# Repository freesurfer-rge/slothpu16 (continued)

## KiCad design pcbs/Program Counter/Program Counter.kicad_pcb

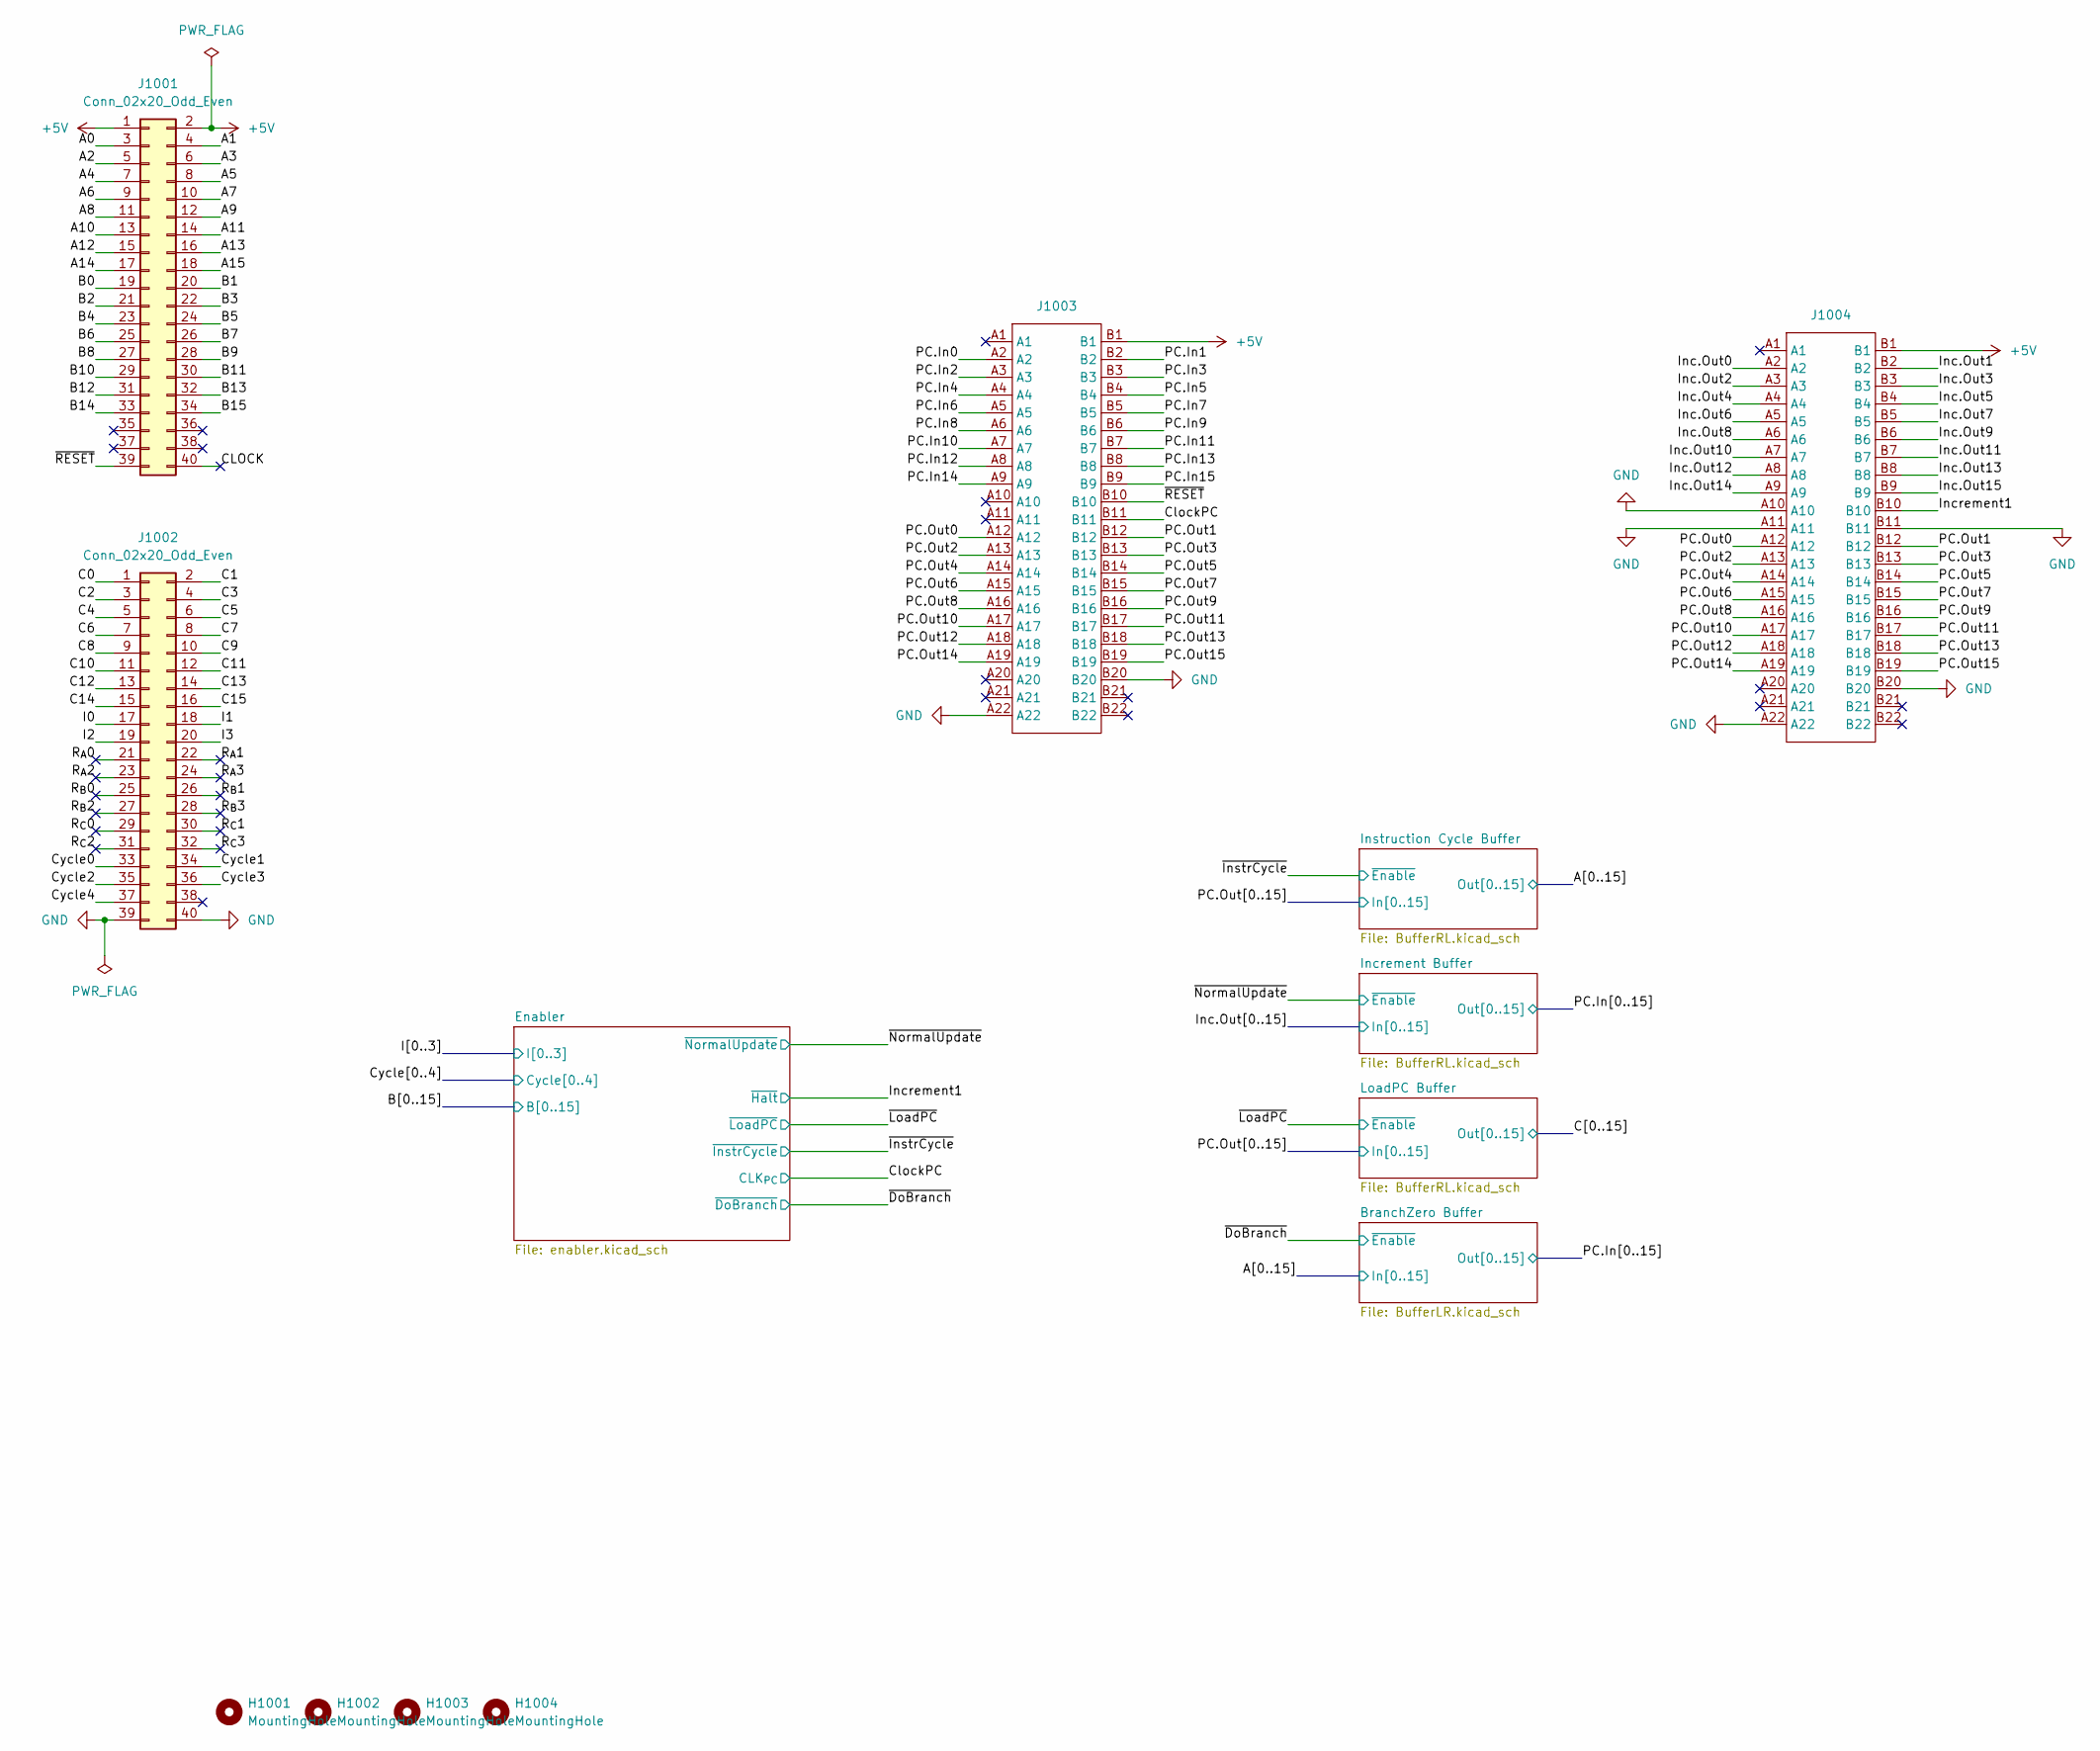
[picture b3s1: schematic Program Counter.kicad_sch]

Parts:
H1001, H1002, H1003, H1004: MountingHole; MountingHole_2.7mm_M2.5_ISO7380
J1001, J1002: Conn_02x20_Odd_Even; PinHeader_2x20_P2.54mm_Vertical
J1003, J1004: TE-5530843-4-Mount

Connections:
+5V: J1001.1, J1001.2, J1003.B1, J1004.B1; also elsewhere on the board
/A0: J1001.3; also elsewhere on the board
/A1: J1001.4; also elsewhere on the board
/A2: J1001.5; also elsewhere on the board
/A3: J1001.6; also elsewhere on the board
/A4: J1001.7; also elsewhere on the board
/A5: J1001.8; also elsewhere on the board
/A6: J1001.9; also elsewhere on the board
/A7: J1001.10; also elsewhere on the board
/A8: J1001.11; also elsewhere on the board
/A9: J1001.12; also elsewhere on the board
/A10: J1001.13; also elsewhere on the board
/A11: J1001.14; also elsewhere on the board
/A12: J1001.15; also elsewhere on the board
/A13: J1001.16; also elsewhere on the board
/A14: J1001.17; also elsewhere on the board
/A15: J1001.18; also elsewhere on the board
/B0: J1001.19; also elsewhere on the board
/B1: J1001.20; also elsewhere on the board
/B2: J1001.21; also elsewhere on the board
/B3: J1001.22; also elsewhere on the board
/B4: J1001.23; also elsewhere on the board
/B5: J1001.24; also elsewhere on the board
/B6: J1001.25; also elsewhere on the board
/B7: J1001.26; also elsewhere on the board
/B8: J1001.27; also elsewhere on the board
/B9: J1001.28; also elsewhere on the board
/B10: J1001.29; also elsewhere on the board
/B11: J1001.30; also elsewhere on the board
/B12: J1001.31; also elsewhere on the board
/B13: J1001.32; also elsewhere on the board
/B14: J1001.33; also elsewhere on the board
/B15: J1001.34; also elsewhere on the board
/C0: J1002.1; also elsewhere on the board
/C1: J1002.2; also elsewhere on the board
/C2: J1002.3; also elsewhere on the board
/C3: J1002.4; also elsewhere on the board
/C4: J1002.5; also elsewhere on the board
/C5: J1002.6; also elsewhere on the board
/C6: J1002.7; also elsewhere on the board
/C7: J1002.8; also elsewhere on the board
/C8: J1002.9; also elsewhere on the board
/C9: J1002.10; also elsewhere on the board
/C10: J1002.11; also elsewhere on the board
/C11: J1002.12; also elsewhere on the board
/C12: J1002.13; also elsewhere on the board
/C13: J1002.14; also elsewhere on the board
/C14: J1002.15; also elsewhere on the board
/C15: J1002.16; also elsewhere on the board
/CLOCK: J1001.40
/ClockPC: J1003.B11; also elsewhere on the board
/Cycle0: J1002.33; also elsewhere on the board
/Cycle1: J1002.34; also elsewhere on the board
/Cycle2: J1002.35; also elsewhere on the board
/Cycle3: J1002.36; also elsewhere on the board
/Cycle4: J1002.37; also elsewhere on the board
/I0: J1002.17; also elsewhere on the board
/I1: J1002.18; also elsewhere on the board
/I2: J1002.19; also elsewhere on the board
/I3: J1002.20; also elsewhere on the board
/Inc.Out0: J1004.A2; also elsewhere on the board
/Inc.Out1: J1004.B2; also elsewhere on the board
/Inc.Out2: J1004.A3; also elsewhere on the board
/Inc.Out3: J1004.B3; also elsewhere on the board
/Inc.Out4: J1004.A4; also elsewhere on the board
/Inc.Out5: J1004.B4; also elsewhere on the board
/Inc.Out6: J1004.A5; also elsewhere on the board
/Inc.Out7: J1004.B5; also elsewhere on the board
/Inc.Out8: J1004.A6; also elsewhere on the board
/Inc.Out9: J1004.B6; also elsewhere on the board
/Inc.Out10: J1004.A7; also elsewhere on the board
/Inc.Out11: J1004.B7; also elsewhere on the board
/Inc.Out12: J1004.A8; also elsewhere on the board
/Inc.Out13: J1004.B8; also elsewhere on the board
/Inc.Out14: J1004.A9; also elsewhere on the board
/Inc.Out15: J1004.B9; also elsewhere on the board
/Increment1: J1004.B10; also elsewhere on the board
/PC.In0: J1003.A2; also elsewhere on the board
/PC.In1: J1003.B2; also elsewhere on the board
/PC.In2: J1003.A3; also elsewhere on the board
/PC.In3: J1003.B3; also elsewhere on the board
/PC.In4: J1003.A4; also elsewhere on the board
/PC.In5: J1003.B4; also elsewhere on the board
/PC.In6: J1003.A5; also elsewhere on the board
/PC.In7: J1003.B5; also elsewhere on the board
/PC.In8: J1003.A6; also elsewhere on the board
/PC.In9: J1003.B6; also elsewhere on the board
/PC.In10: J1003.A7; also elsewhere on the board
/PC.In11: J1003.B7; also elsewhere on the board
/PC.In12: J1003.A8; also elsewhere on the board
/PC.In13: J1003.B8; also elsewhere on the board
/PC.In14: J1003.A9; also elsewhere on the board
/PC.In15: J1003.B9; also elsewhere on the board
/PC.Out0: J1003.A12, J1004.A12; also elsewhere on the board
/PC.Out1: J1003.B12, J1004.B12; also elsewhere on the board
/PC.Out2: J1003.A13, J1004.A13; also elsewhere on the board
/PC.Out3: J1003.B13, J1004.B13; also elsewhere on the board
/PC.Out4: J1003.A14, J1004.A14; also elsewhere on the board
/PC.Out5: J1003.B14, J1004.B14; also elsewhere on the board
/PC.Out6: J1003.A15, J1004.A15; also elsewhere on the board
/PC.Out7: J1003.B15, J1004.B15; also elsewhere on the board
/PC.Out8: J1003.A16, J1004.A16; also elsewhere on the board
/PC.Out9: J1003.B16, J1004.B16; also elsewhere on the board
/PC.Out10: J1003.A17, J1004.A17; also elsewhere on the board
/PC.Out11: J1003.B17, J1004.B17; also elsewhere on the board
/PC.Out12: J1003.A18, J1004.A18; also elsewhere on the board
/PC.Out13: J1003.B18, J1004.B18; also elsewhere on the board
/PC.Out14: J1003.A19, J1004.A19; also elsewhere on the board
/PC.Out15: J1003.B19, J1004.B19; also elsewhere on the board
/R_{A}0: J1002.21
/R_{A}1: J1002.22
/R_{A}2: J1002.23
/R_{A}3: J1002.24
/R_{B}0: J1002.25
/R_{B}1: J1002.26
/R_{B}2: J1002.27
/R_{B}3: J1002.28
/R_{C}0: J1002.29
/R_{C}1: J1002.30
/R_{C}2: J1002.31
/R_{C}3: J1002.32
/~RESET: J1001.39, J1003.B10
GND: J1002.39, J1002.40, J1003.A22, J1003.B20, J1004.A10, J1004.A11, J1004.A22, J1004.B11, J1004.B20; also elsewhere on the board

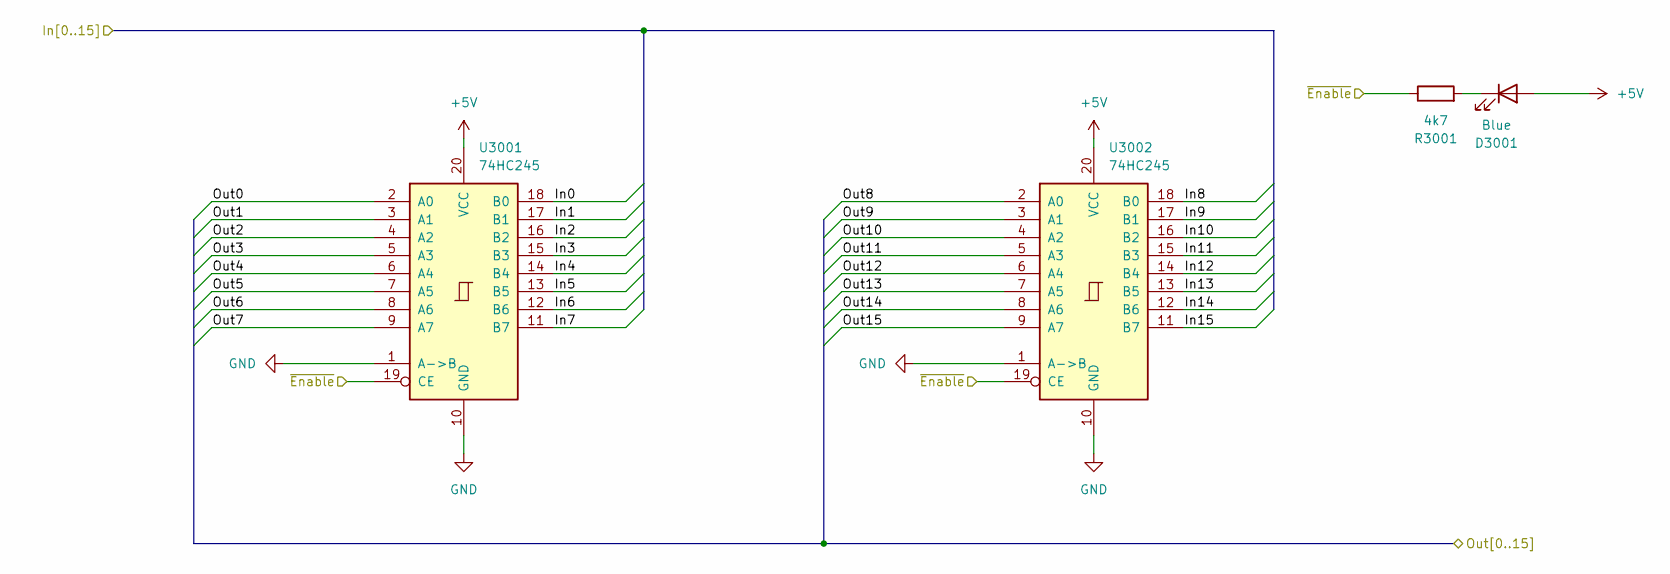
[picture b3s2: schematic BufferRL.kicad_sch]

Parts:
D3001: Blue; LED_0603_1608Metric; LCSC C72041
R3001: 4k7; R_0603_1608Metric; LCSC C23162
U3001, U3002: 74HC245; SOIC-20W_7.5x12.8mm_P1.27mm; LCSC C5625

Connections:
+5V: D3001.2 (A), U3001.20 (VCC), U3002.20 (VCC); also elsewhere on the board
/Inc.Out0: U3001.18 (B0); also elsewhere on the board
/Inc.Out1: U3001.17 (B1); also elsewhere on the board
/Inc.Out2: U3001.16 (B2); also elsewhere on the board
/Inc.Out3: U3001.15 (B3); also elsewhere on the board
/Inc.Out4: U3001.14 (B4); also elsewhere on the board
/Inc.Out5: U3001.13 (B5); also elsewhere on the board
/Inc.Out6: U3001.12 (B6); also elsewhere on the board
/Inc.Out7: U3001.11 (B7); also elsewhere on the board
/Inc.Out8: U3002.18 (B0); also elsewhere on the board
/Inc.Out9: U3002.17 (B1); also elsewhere on the board
/Inc.Out10: U3002.16 (B2); also elsewhere on the board
/Inc.Out11: U3002.15 (B3); also elsewhere on the board
/Inc.Out12: U3002.14 (B4); also elsewhere on the board
/Inc.Out13: U3002.13 (B5); also elsewhere on the board
/Inc.Out14: U3002.12 (B6); also elsewhere on the board
/Inc.Out15: U3002.11 (B7); also elsewhere on the board
/PC.In0: U3001.2 (A0); also elsewhere on the board
/PC.In1: U3001.3 (A1); also elsewhere on the board
/PC.In2: U3001.4 (A2); also elsewhere on the board
/PC.In3: U3001.5 (A3); also elsewhere on the board
/PC.In4: U3001.6 (A4); also elsewhere on the board
/PC.In5: U3001.7 (A5); also elsewhere on the board
/PC.In6: U3001.8 (A6); also elsewhere on the board
/PC.In7: U3001.9 (A7); also elsewhere on the board
/PC.In8: U3002.2 (A0); also elsewhere on the board
/PC.In9: U3002.3 (A1); also elsewhere on the board
/PC.In10: U3002.4 (A2); also elsewhere on the board
/PC.In11: U3002.5 (A3); also elsewhere on the board
/PC.In12: U3002.6 (A4); also elsewhere on the board
/PC.In13: U3002.7 (A5); also elsewhere on the board
/PC.In14: U3002.8 (A6); also elsewhere on the board
/PC.In15: U3002.9 (A7); also elsewhere on the board
/~NormalUpdate: R3001.1, U3001.19 (CE), U3002.19 (CE); also elsewhere on the board
GND: U3001.1 (A->B), U3001.10 (GND), U3002.1 (A->B), U3002.10 (GND); also elsewhere on the board
unnamed: D3001.1 (K), R3001.2

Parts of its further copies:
D2001, D4001: Blue; LED_0603_1608Metric; LCSC C72041
R2001, R4001: 4k7; R_0603_1608Metric; LCSC C23162
U2001, U2002, U4001, U4002: 74HC245; SOIC-20W_7.5x12.8mm_P1.27mm; LCSC C5625

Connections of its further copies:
+5V: D2001.2 (A), D4001.2 (A), U2001.20 (VCC), U2002.20 (VCC), U4001.20 (VCC), U4002.20 (VCC); also elsewhere on the board
/A0: U2001.2 (A0); also elsewhere on the board
/A1: U2001.3 (A1); also elsewhere on the board
/A2: U2001.4 (A2); also elsewhere on the board
/A3: U2001.5 (A3); also elsewhere on the board
/A4: U2001.6 (A4); also elsewhere on the board
/A5: U2001.7 (A5); also elsewhere on the board
/A6: U2001.8 (A6); also elsewhere on the board
/A7: U2001.9 (A7); also elsewhere on the board
/A8: U2002.2 (A0); also elsewhere on the board
/A9: U2002.3 (A1); also elsewhere on the board
/A10: U2002.4 (A2); also elsewhere on the board
/A11: U2002.5 (A3); also elsewhere on the board
/A12: U2002.6 (A4); also elsewhere on the board
/A13: U2002.7 (A5); also elsewhere on the board
/A14: U2002.8 (A6); also elsewhere on the board
/A15: U2002.9 (A7); also elsewhere on the board
/C0: U4001.2 (A0); also elsewhere on the board
/C1: U4001.3 (A1); also elsewhere on the board
/C2: U4001.4 (A2); also elsewhere on the board
/C3: U4001.5 (A3); also elsewhere on the board
/C4: U4001.6 (A4); also elsewhere on the board
/C5: U4001.7 (A5); also elsewhere on the board
/C6: U4001.8 (A6); also elsewhere on the board
/C7: U4001.9 (A7); also elsewhere on the board
/C8: U4002.2 (A0); also elsewhere on the board
/C9: U4002.3 (A1); also elsewhere on the board
/C10: U4002.4 (A2); also elsewhere on the board
/C11: U4002.5 (A3); also elsewhere on the board
/C12: U4002.6 (A4); also elsewhere on the board
/C13: U4002.7 (A5); also elsewhere on the board
/C14: U4002.8 (A6); also elsewhere on the board
/C15: U4002.9 (A7); also elsewhere on the board
/PC.Out0: U2001.18 (B0), U4001.18 (B0); also elsewhere on the board
/PC.Out1: U2001.17 (B1), U4001.17 (B1); also elsewhere on the board
/PC.Out2: U2001.16 (B2), U4001.16 (B2); also elsewhere on the board
/PC.Out3: U2001.15 (B3), U4001.15 (B3); also elsewhere on the board
/PC.Out4: U2001.14 (B4), U4001.14 (B4); also elsewhere on the board
/PC.Out5: U2001.13 (B5), U4001.13 (B5); also elsewhere on the board
/PC.Out6: U2001.12 (B6), U4001.12 (B6); also elsewhere on the board
/PC.Out7: U2001.11 (B7), U4001.11 (B7); also elsewhere on the board
/PC.Out8: U2002.18 (B0), U4002.18 (B0); also elsewhere on the board
/PC.Out9: U2002.17 (B1), U4002.17 (B1); also elsewhere on the board
/PC.Out10: U2002.16 (B2), U4002.16 (B2); also elsewhere on the board
/PC.Out11: U2002.15 (B3), U4002.15 (B3); also elsewhere on the board
/PC.Out12: U2002.14 (B4), U4002.14 (B4); also elsewhere on the board
/PC.Out13: U2002.13 (B5), U4002.13 (B5); also elsewhere on the board
/PC.Out14: U2002.12 (B6), U4002.12 (B6); also elsewhere on the board
/PC.Out15: U2002.11 (B7), U4002.11 (B7); also elsewhere on the board
/~InstrCycle: R2001.1, U2001.19 (CE), U2002.19 (CE); also elsewhere on the board
/~LoadPC: R4001.1, U4001.19 (CE), U4002.19 (CE); also elsewhere on the board
GND: U2001.1 (A->B), U2001.10 (GND), U2002.1 (A->B), U2002.10 (GND), U4001.1 (A->B), U4001.10 (GND), U4002.1 (A->B), U4002.10 (GND); also elsewhere on the board
unnamed: D2001.1 (K), R2001.2
unnamed: D4001.1 (K), R4001.2

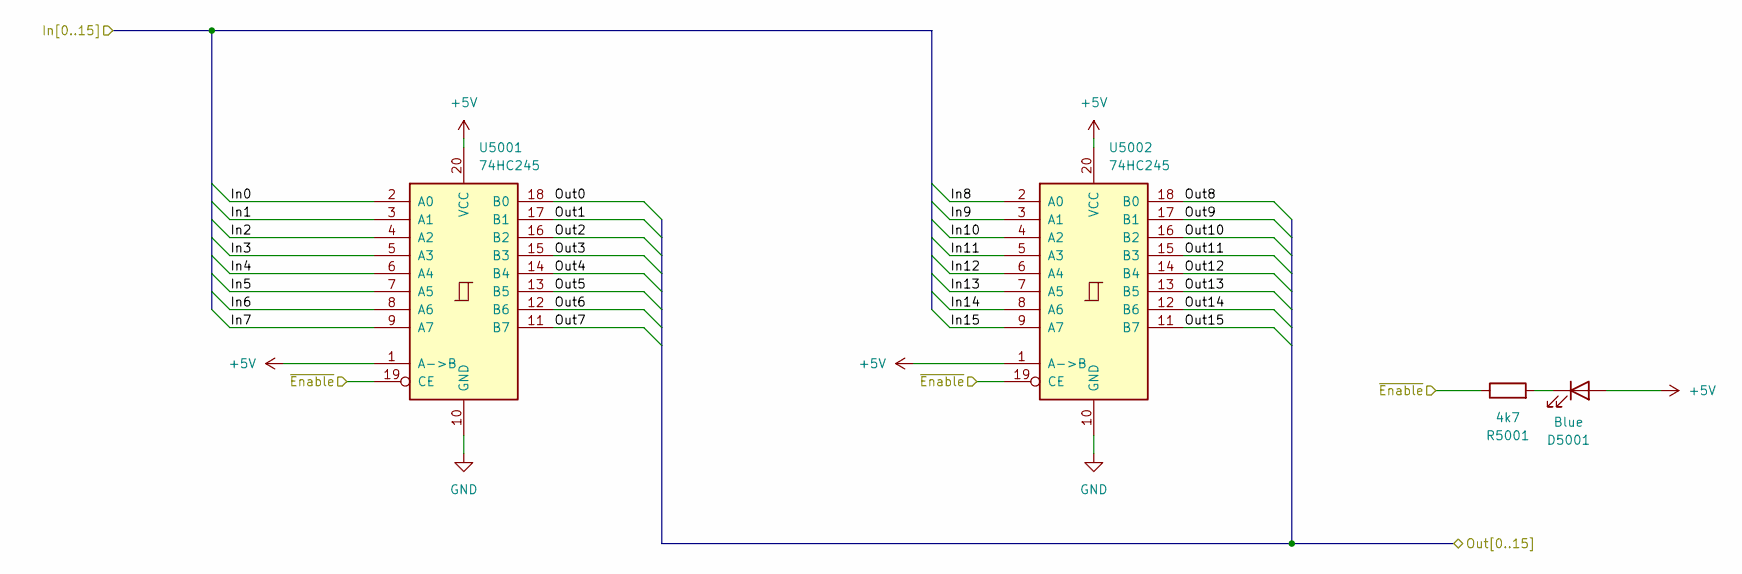
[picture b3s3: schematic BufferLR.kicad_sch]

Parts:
D5001: Blue; LED_0603_1608Metric; LCSC C72041
R5001: 4k7; R_0603_1608Metric; LCSC C23162
U5001, U5002: 74HC245; SOIC-20W_7.5x12.8mm_P1.27mm; LCSC C5625

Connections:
+5V: D5001.2 (A), U5001.1 (A->B), U5001.20 (VCC), U5002.1 (A->B), U5002.20 (VCC); also elsewhere on the board
/A0: U5001.2 (A0); also elsewhere on the board
/A1: U5001.3 (A1); also elsewhere on the board
/A2: U5001.4 (A2); also elsewhere on the board
/A3: U5001.5 (A3); also elsewhere on the board
/A4: U5001.6 (A4); also elsewhere on the board
/A5: U5001.7 (A5); also elsewhere on the board
/A6: U5001.8 (A6); also elsewhere on the board
/A7: U5001.9 (A7); also elsewhere on the board
/A8: U5002.2 (A0); also elsewhere on the board
/A9: U5002.3 (A1); also elsewhere on the board
/A10: U5002.4 (A2); also elsewhere on the board
/A11: U5002.5 (A3); also elsewhere on the board
/A12: U5002.6 (A4); also elsewhere on the board
/A13: U5002.7 (A5); also elsewhere on the board
/A14: U5002.8 (A6); also elsewhere on the board
/A15: U5002.9 (A7); also elsewhere on the board
/PC.In0: U5001.18 (B0); also elsewhere on the board
/PC.In1: U5001.17 (B1); also elsewhere on the board
/PC.In2: U5001.16 (B2); also elsewhere on the board
/PC.In3: U5001.15 (B3); also elsewhere on the board
/PC.In4: U5001.14 (B4); also elsewhere on the board
/PC.In5: U5001.13 (B5); also elsewhere on the board
/PC.In6: U5001.12 (B6); also elsewhere on the board
/PC.In7: U5001.11 (B7); also elsewhere on the board
/PC.In8: U5002.18 (B0); also elsewhere on the board
/PC.In9: U5002.17 (B1); also elsewhere on the board
/PC.In10: U5002.16 (B2); also elsewhere on the board
/PC.In11: U5002.15 (B3); also elsewhere on the board
/PC.In12: U5002.14 (B4); also elsewhere on the board
/PC.In13: U5002.13 (B5); also elsewhere on the board
/PC.In14: U5002.12 (B6); also elsewhere on the board
/PC.In15: U5002.11 (B7); also elsewhere on the board
/~DoBranch: R5001.1, U5001.19 (CE), U5002.19 (CE); also elsewhere on the board
GND: U5001.10 (GND), U5002.10 (GND); also elsewhere on the board
unnamed: D5001.1 (K), R5001.2

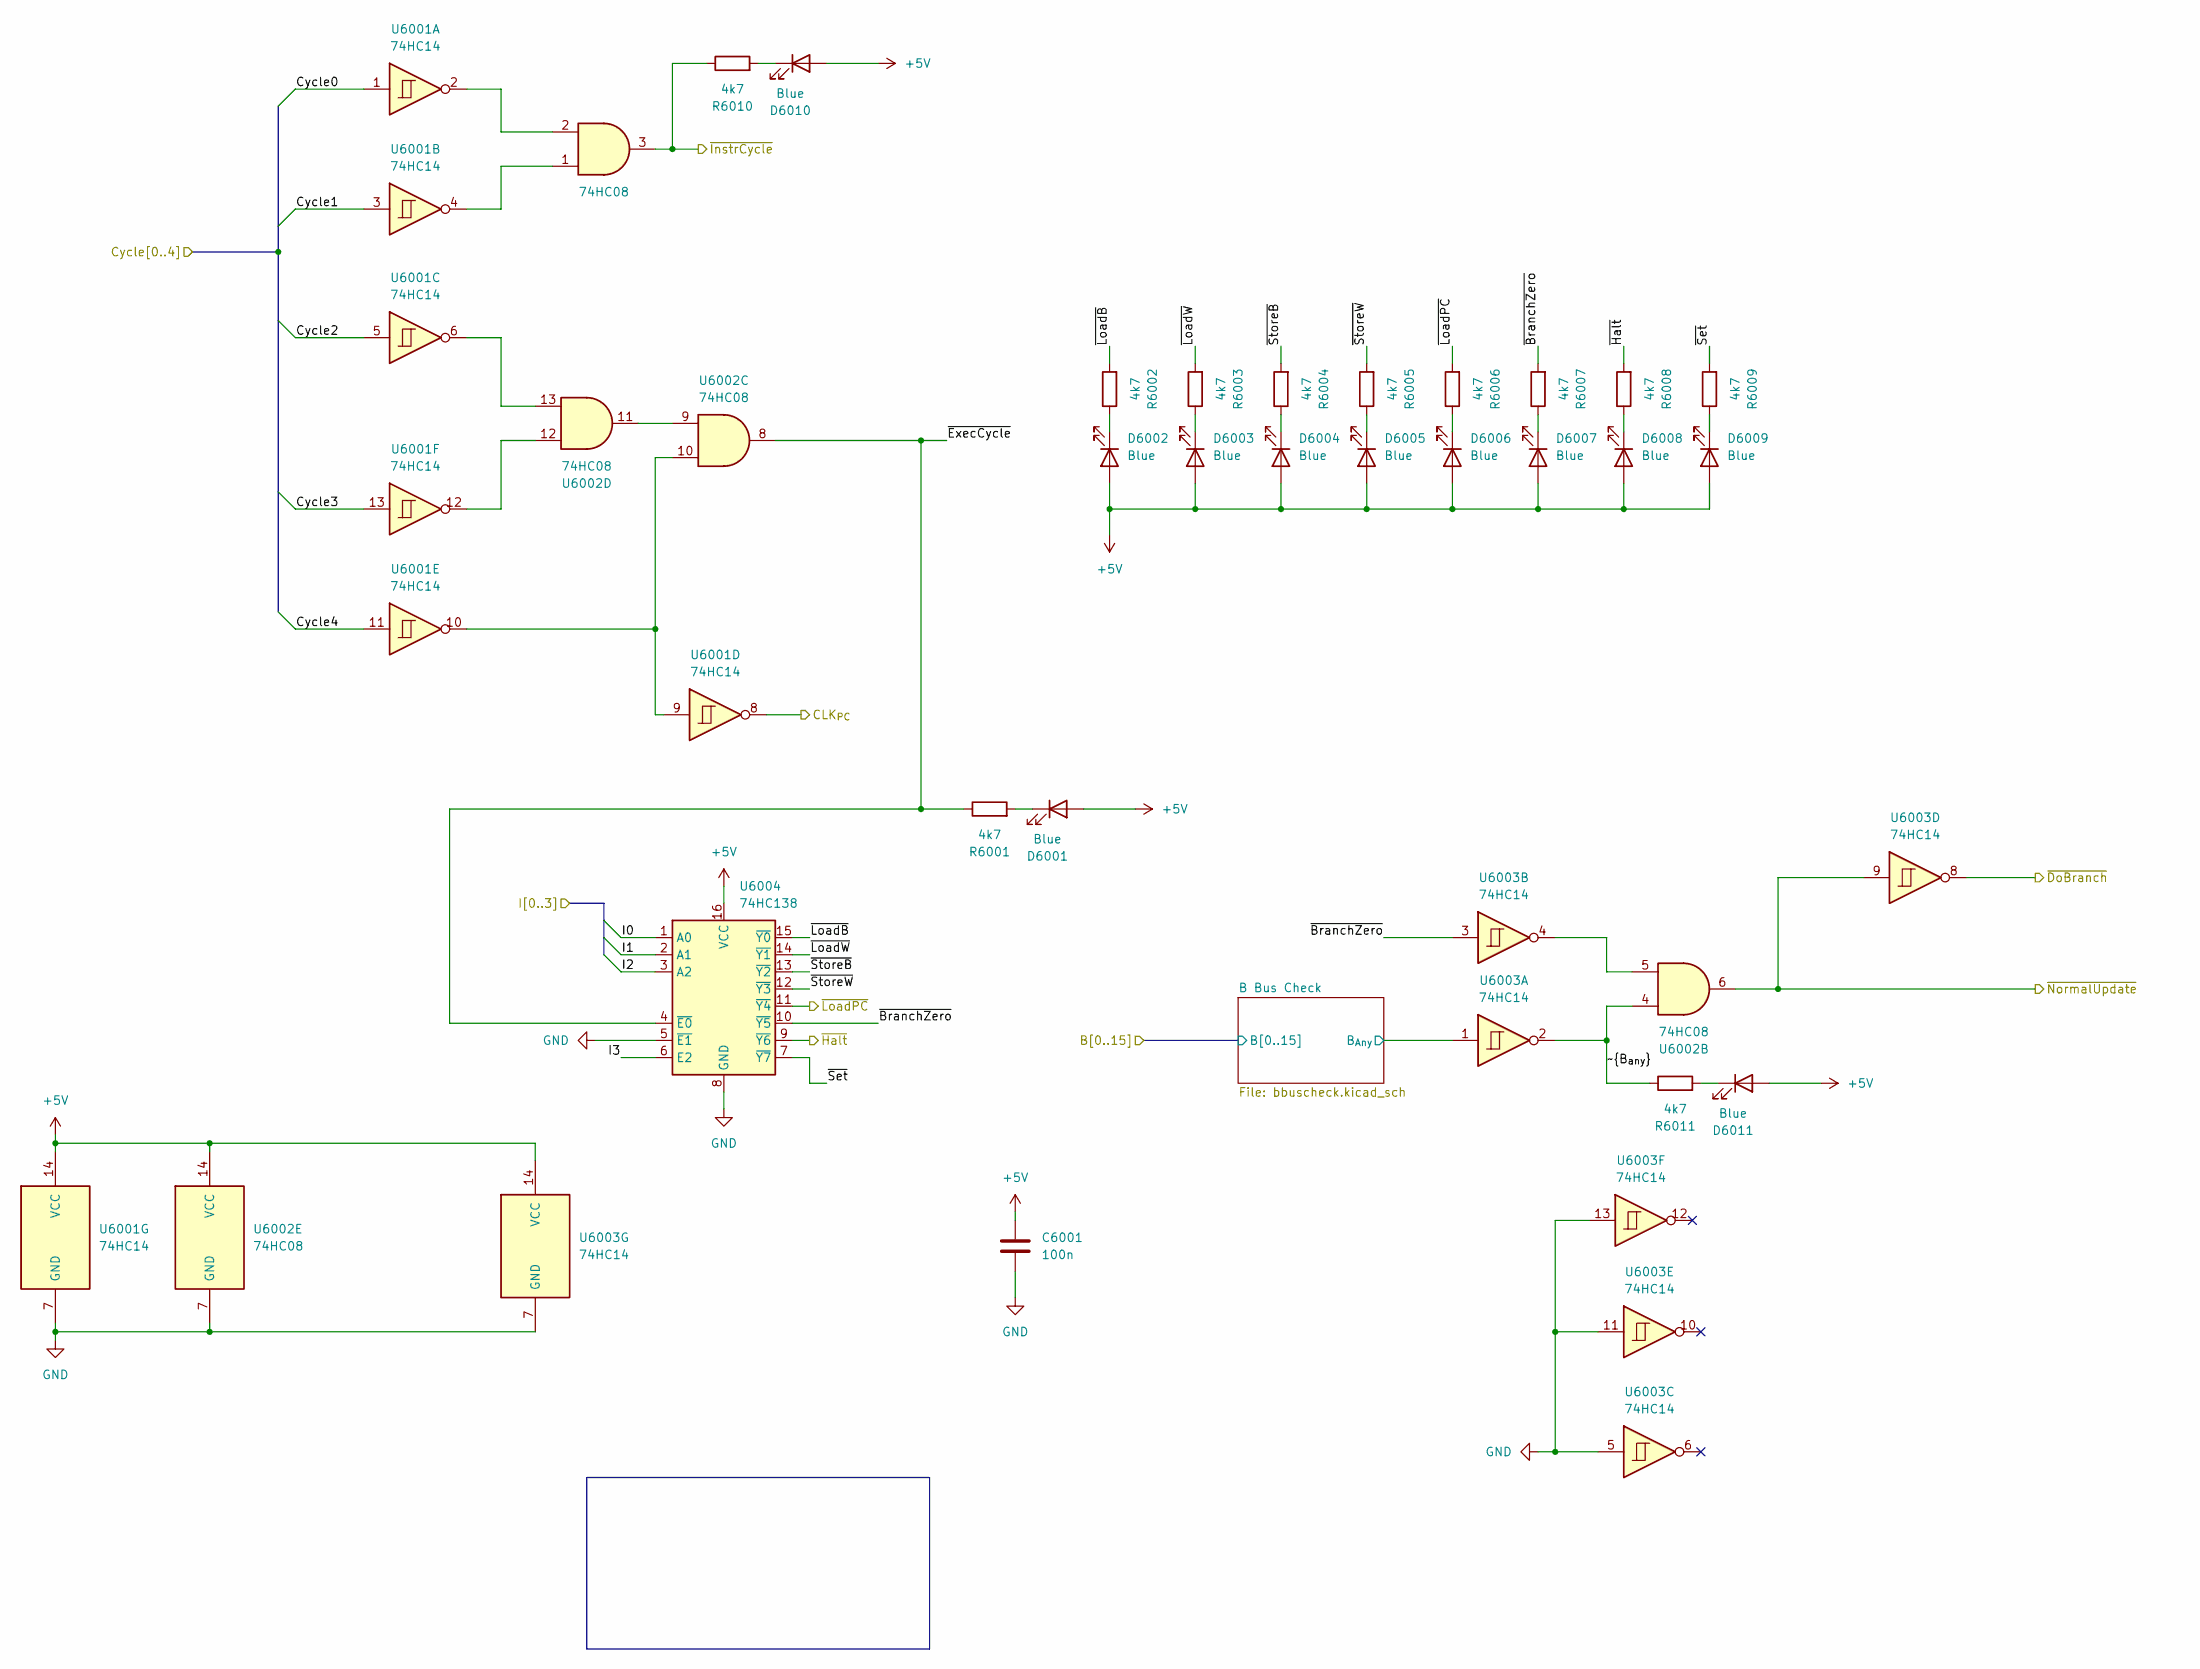
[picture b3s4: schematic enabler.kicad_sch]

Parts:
C6001: 100n; C_0603_1608Metric; LCSC C14663
D6001, D6002, D6003, D6004, D6005, D6006, D6007, D6008, D6009, D6010, D6011: Blue; LED_0603_1608Metric; LCSC C72041
R6001, R6002, R6003, R6004, R6005, R6006, R6007, R6008, R6009, R6010, R6011: 4k7; R_0603_1608Metric; LCSC C23162
U6001, U6003: 74HC14; SOIC-14_3.9x8.7mm_P1.27mm; LCSC C5605
U6002: 74HC08; SOIC-14_3.9x8.7mm_P1.27mm; LCSC C5593
U6004: 74HC138; DIP-16_W7.62mm_Socket

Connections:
+5V: C6001.1, D6001.2 (A), D6002.2 (A), D6003.2 (A), D6004.2 (A), D6005.2 (A), D6006.2 (A), D6007.2 (A), D6008.2 (A), D6009.2 (A), D6010.2 (A), D6011.2 (A), U6001.14 (VCC), U6002.14 (VCC), U6003.14 (VCC), U6004.16 (VCC); also elsewhere on the board
/ClockPC: U6001.8; also elsewhere on the board
/Cycle0: U6001.1; also elsewhere on the board
/Cycle1: U6001.3; also elsewhere on the board
/Cycle2: U6001.5; also elsewhere on the board
/Cycle3: U6001.13; also elsewhere on the board
/Cycle4: U6001.11; also elsewhere on the board
/Enabler/B Bus Check/B_{Any}: U6003.1; also elsewhere on the board
/Enabler/~B_{any}: R6011.1, U6002.4, U6003.2
/Enabler/~BranchZero: R6007.2, U6003.3, U6004.10 (~Y5)
/Enabler/~ExecCycle: R6001.1, U6002.8, U6004.4 (~E0)
/Enabler/~LoadB: R6002.2, U6004.15 (~Y0)
/Enabler/~LoadW: R6003.2, U6004.14 (~Y1)
/Enabler/~Set: R6009.2, U6004.7 (~Y7)
/Enabler/~StoreB: R6004.2, U6004.13 (~Y2)
/Enabler/~StoreW: R6005.2, U6004.12 (~Y3)
/I0: U6004.1 (A0); also elsewhere on the board
/I1: U6004.2 (A1); also elsewhere on the board
/I2: U6004.3 (A2); also elsewhere on the board
/I3: U6004.6 (E2); also elsewhere on the board
/Increment1: R6008.2, U6004.9 (~Y6); also elsewhere on the board
/~DoBranch: U6003.8; also elsewhere on the board
/~InstrCycle: R6010.1, U6002.3; also elsewhere on the board
/~LoadPC: R6006.2, U6004.11 (~Y4); also elsewhere on the board
/~NormalUpdate: U6002.6, U6003.9; also elsewhere on the board
GND: C6001.2, U6001.7 (GND), U6002.7 (GND), U6003.5, U6003.7 (GND), U6003.11, U6003.13, U6004.5 (~E1), U6004.8 (GND); also elsewhere on the board
unnamed: D6001.1 (K), R6001.2
unnamed: D6002.1 (K), R6002.1
unnamed: D6003.1 (K), R6003.1
unnamed: D6004.1 (K), R6004.1
unnamed: D6005.1 (K), R6005.1
unnamed: D6006.1 (K), R6006.1
unnamed: D6007.1 (K), R6007.1
unnamed: D6008.1 (K), R6008.1
unnamed: D6009.1 (K), R6009.1
unnamed: D6010.1 (K), R6010.2
unnamed: D6011.1 (K), R6011.2
unnamed: U6001.2, U6002.2
unnamed: U6001.4, U6002.1
unnamed: U6001.6, U6002.13
unnamed: U6001.9, U6001.10, U6002.10
unnamed: U6001.12, U6002.12
unnamed: U6002.5, U6003.4
unnamed: U6002.9, U6002.11

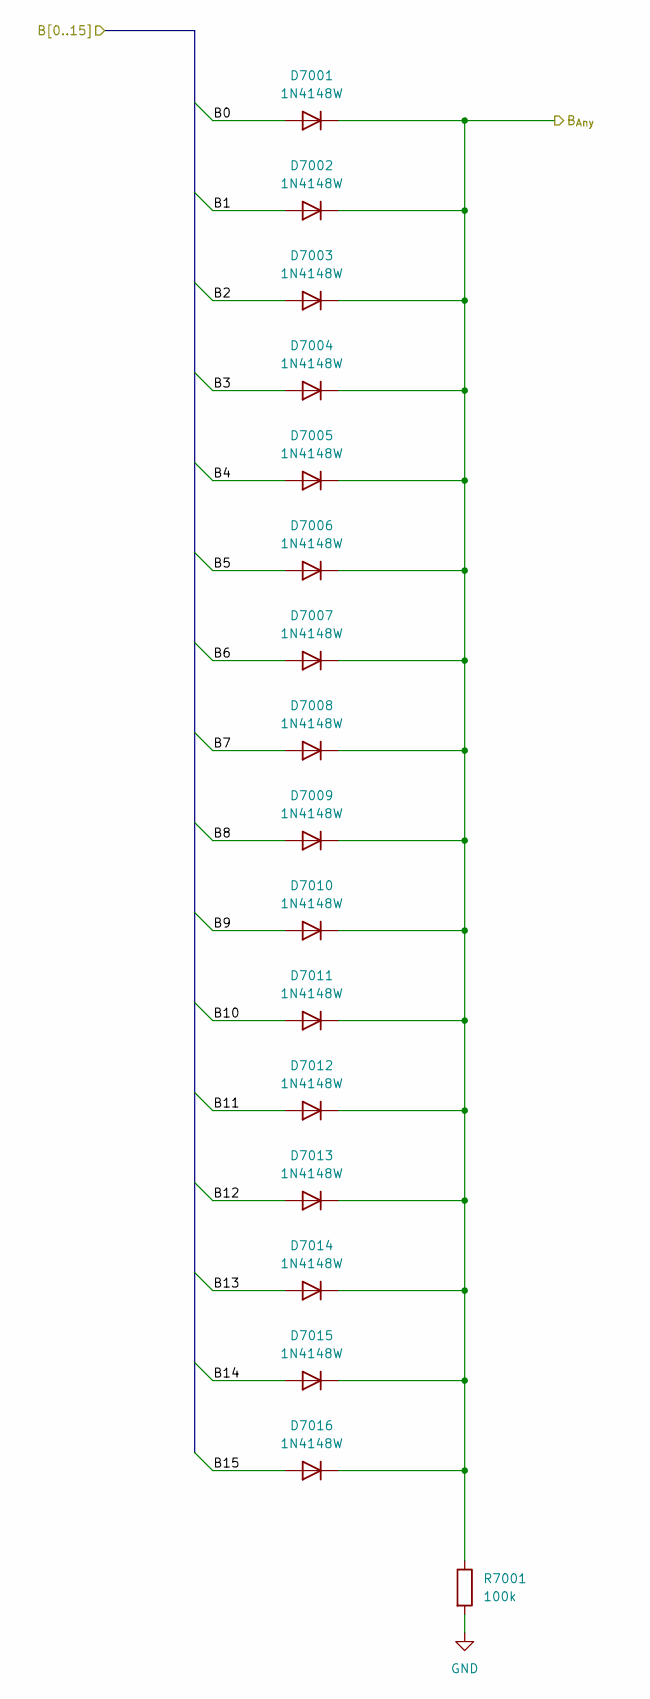
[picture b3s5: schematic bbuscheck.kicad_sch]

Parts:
D7001, D7002, D7003, D7004, D7005, D7006, D7007, D7008, D7009, D7010, D7011, D7012, D7013, D7014, D7015, D7016: 1N4148W; D_SOD-323; LCSC C2128
R7001: 100k; R_0603_1608Metric; LCSC C25803

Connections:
/B0: D7001.2 (A); also elsewhere on the board
/B1: D7002.2 (A); also elsewhere on the board
/B2: D7003.2 (A); also elsewhere on the board
/B3: D7004.2 (A); also elsewhere on the board
/B4: D7005.2 (A); also elsewhere on the board
/B5: D7006.2 (A); also elsewhere on the board
/B6: D7007.2 (A); also elsewhere on the board
/B7: D7008.2 (A); also elsewhere on the board
/B8: D7009.2 (A); also elsewhere on the board
/B9: D7010.2 (A); also elsewhere on the board
/B10: D7011.2 (A); also elsewhere on the board
/B11: D7012.2 (A); also elsewhere on the board
/B12: D7013.2 (A); also elsewhere on the board
/B13: D7014.2 (A); also elsewhere on the board
/B14: D7015.2 (A); also elsewhere on the board
/B15: D7016.2 (A); also elsewhere on the board
/Enabler/B Bus Check/B_{Any}: D7001.1 (K), D7002.1 (K), D7003.1 (K), D7004.1 (K), D7005.1 (K), D7006.1 (K), D7007.1 (K), D7008.1 (K), D7009.1 (K), D7010.1 (K), D7011.1 (K), D7012.1 (K), D7013.1 (K), D7014.1 (K), D7015.1 (K), D7016.1 (K), R7001.1; also elsewhere on the board
GND: R7001.2; also elsewhere on the board

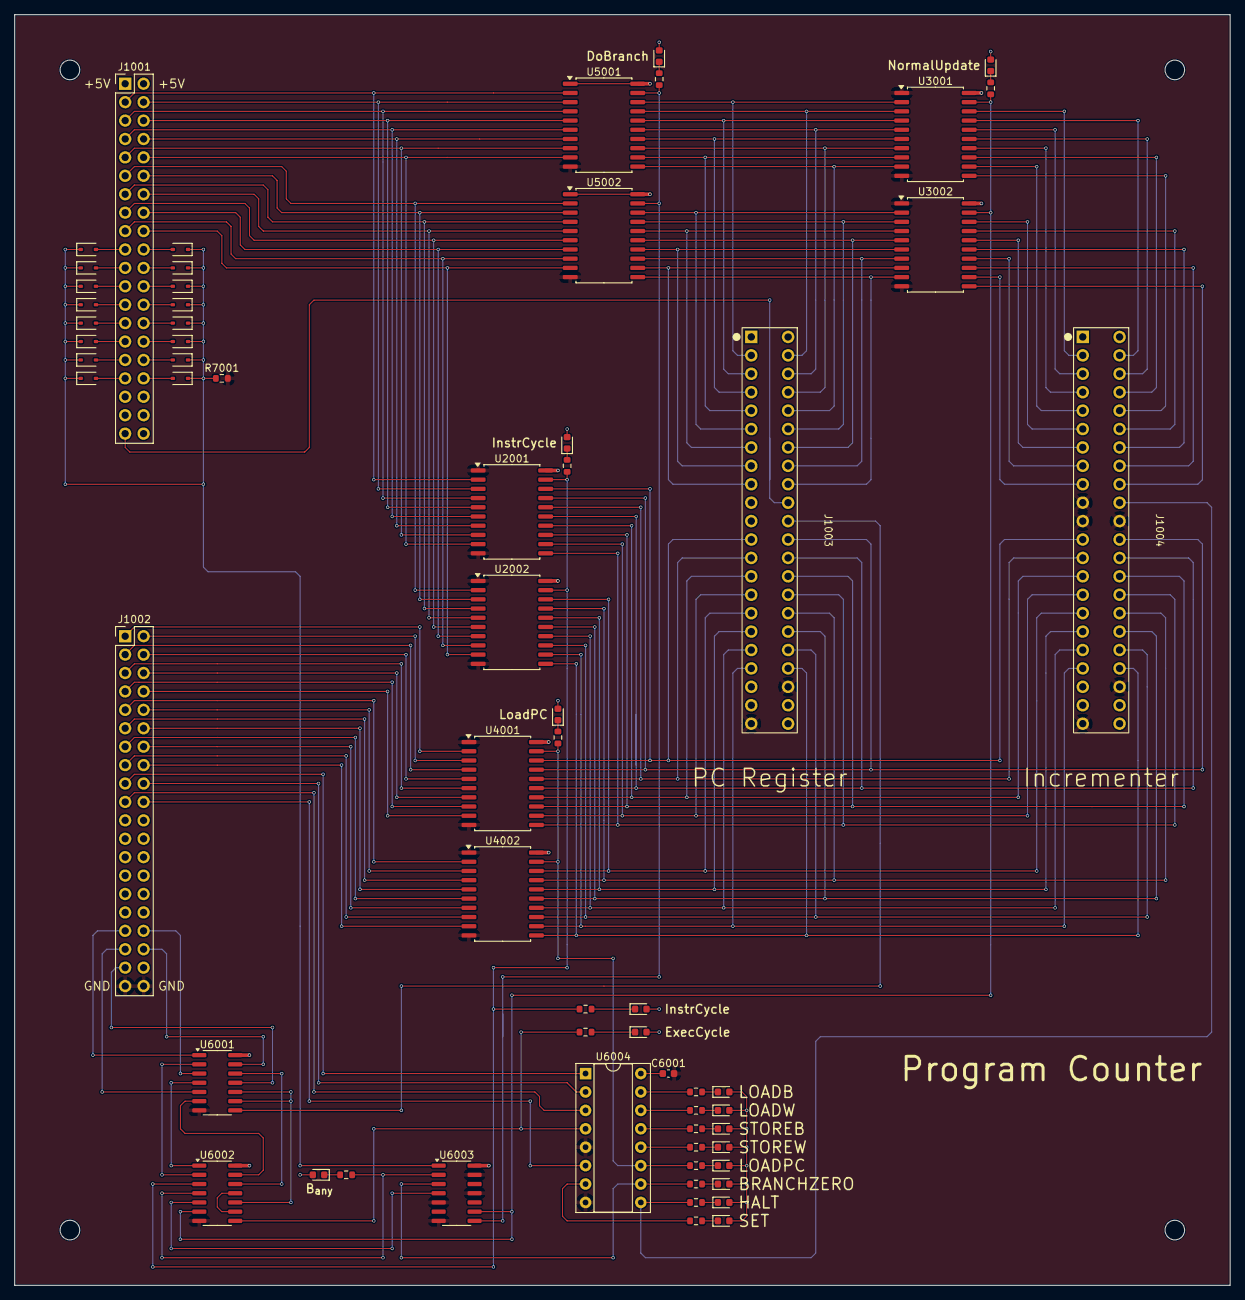
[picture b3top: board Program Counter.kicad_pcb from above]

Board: 2 copper layers, 167.6 x 175.3 mm, 68 parts (0 on the bottom side), 145 nets.
